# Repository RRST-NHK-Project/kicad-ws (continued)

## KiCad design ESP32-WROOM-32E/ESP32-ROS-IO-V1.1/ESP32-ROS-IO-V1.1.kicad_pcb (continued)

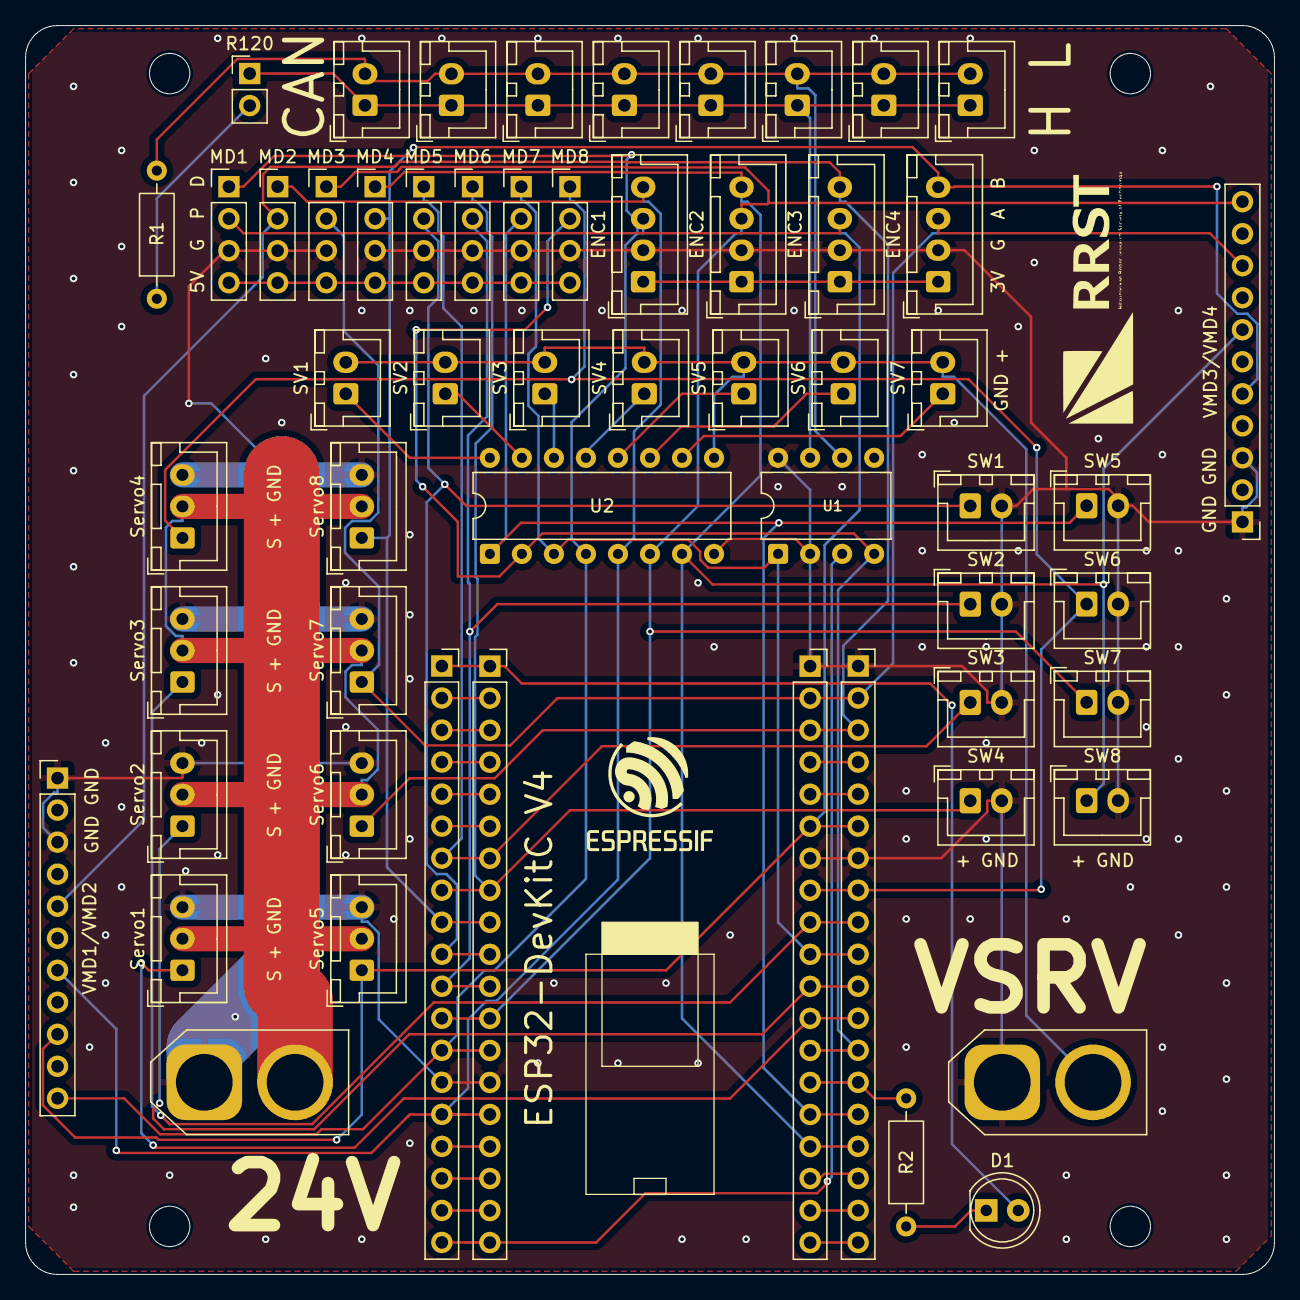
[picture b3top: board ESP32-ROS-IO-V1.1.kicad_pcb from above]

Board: 2 copper layers, 99.1 x 99.1 mm, 57 parts (0 on the bottom side), 51 nets.

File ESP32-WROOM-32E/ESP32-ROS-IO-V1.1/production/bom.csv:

Designator,Footprint,Quantity,Value,LCSC Part #
"CAN_BUS1, CAN_BUS2, CAN_BUS3, CAN_BUS4, CAN_BUS5, CAN_BUS6, CAN_BUS7, CAN_BUS8",JST_XH_B2B-XH-A_1x02_P2.50mm_Vertical,8,CAN_BUS,
D1,LED_D5.0mm,1,LED,
ENC1,JST_XH_B4B-XH-A_1x04_P2.50mm_Vertical,1,ENC1,
ENC2,JST_XH_B4B-XH-A_1x04_P2.50mm_Vertical,1,ENC2,
ENC3,JST_XH_B4B-XH-A_1x04_P2.50mm_Vertical,1,ENC3,
ENC4,JST_XH_B4B-XH-A_1x04_P2.50mm_Vertical,1,ENC4,
"J1, J2, J3, J4",PinSocket_1x19_P2.54mm_Vertical,4,Conn_01x19_Socket,
"J12, J13",AMASS_XT60-M_1x02_P7.20mm_Vertical,2,XT60-M,
MD1,PinHeader_1x04_P2.54mm_Vertical,1,MD1,
MD2,PinHeader_1x04_P2.54mm_Vertical,1,MD2,
MD3,PinHeader_1x04_P2.54mm_Vertical,1,MD3,
MD4,PinHeader_1x04_P2.54mm_Vertical,1,MD4,
MD5,PinHeader_1x04_P2.54mm_Vertical,1,MD5,
MD6,PinHeader_1x04_P2.54mm_Vertical,1,MD6,
MD7,PinHeader_1x04_P2.54mm_Vertical,1,MD7,
MD8,PinHeader_1x04_P2.54mm_Vertical,1,MD8,
R1,R_Axial_DIN0207_L6.3mm_D2.5mm_P10.16mm_Horizontal,1,120,
R120,PinHeader_1x02_P2.54mm_Vertical,1,R120,
R2,R_Axial_DIN0207_L6.3mm_D2.5mm_P10.16mm_Horizontal,1,330,
SERVO1,JST_XH_B3B-XH-A_1x03_P2.50mm_Vertical,1,Servo1,
SERVO2,JST_XH_B3B-XH-A_1x03_P2.50mm_Vertical,1,Servo2,
SERVO3,JST_XH_B3B-XH-A_1x03_P2.50mm_Vertical,1,Servo3,
SERVO4,JST_XH_B3B-XH-A_1x03_P2.50mm_Vertical,1,Servo4,
SERVO5,JST_XH_B3B-XH-A_1x03_P2.50mm_Vertical,1,Servo5,
SERVO6,JST_XH_B3B-XH-A_1x03_P2.50mm_Vertical,1,Servo6,
SERVO7,JST_XH_B3B-XH-A_1x03_P2.50mm_Vertical,1,Servo7,
SERVO8,JST_XH_B3B-XH-A_1x03_P2.50mm_Vertical,1,Servo8,
SV1,JST_XH_B2B-XH-A_1x02_P2.50mm_Vertical,1,SV1,
SV2,JST_XH_B2B-XH-A_1x02_P2.50mm_Vertical,1,SV2,
SV3,JST_XH_B2B-XH-A_1x02_P2.50mm_Vertical,1,SV3,
SV4,JST_XH_B2B-XH-A_1x02_P2.50mm_Vertical,1,SV4,
SV5,JST_XH_B2B-XH-A_1x02_P2.50mm_Vertical,1,SV5,
SV6,JST_XH_B2B-XH-A_1x02_P2.50mm_Vertical,1,SV6,
SV7,JST_XH_B2B-XH-A_1x02_P2.50mm_Vertical,1,SV7,
SW1,JST_XH_B2B-XH-A_1x02_P2.50mm_Vertical,1,SW1,
SW2,JST_XH_B2B-XH-A_1x02_P2.50mm_Vertical,1,SW2,
SW3,JST_XH_B2B-XH-A_1x02_P2.50mm_Vertical,1,SW3,
SW4,JST_XH_B2B-XH-A_1x02_P2.50mm_Vertical,1,SW4,
SW5,JST_XH_B2B-XH-A_1x02_P2.50mm_Vertical,1,SW5,
SW6,JST_XH_B2B-XH-A_1x02_P2.50mm_Vertical,1,SW6,
"SW7, SW8",JST_XH_B2B-XH-A_1x02_P2.50mm_Vertical,2,SW7,
U1,DIP-8_W7.62mm,1,~,
U2,DIP-16_W7.62mm,1,~,
VMD1/VMD2,PinHeader_1x11_P2.54mm_Vertical,1,VMD1/VMD2,
VMD3/VMD4,PinHeader_1x11_P2.54mm_Vertical,1,VMD3/VMD4,

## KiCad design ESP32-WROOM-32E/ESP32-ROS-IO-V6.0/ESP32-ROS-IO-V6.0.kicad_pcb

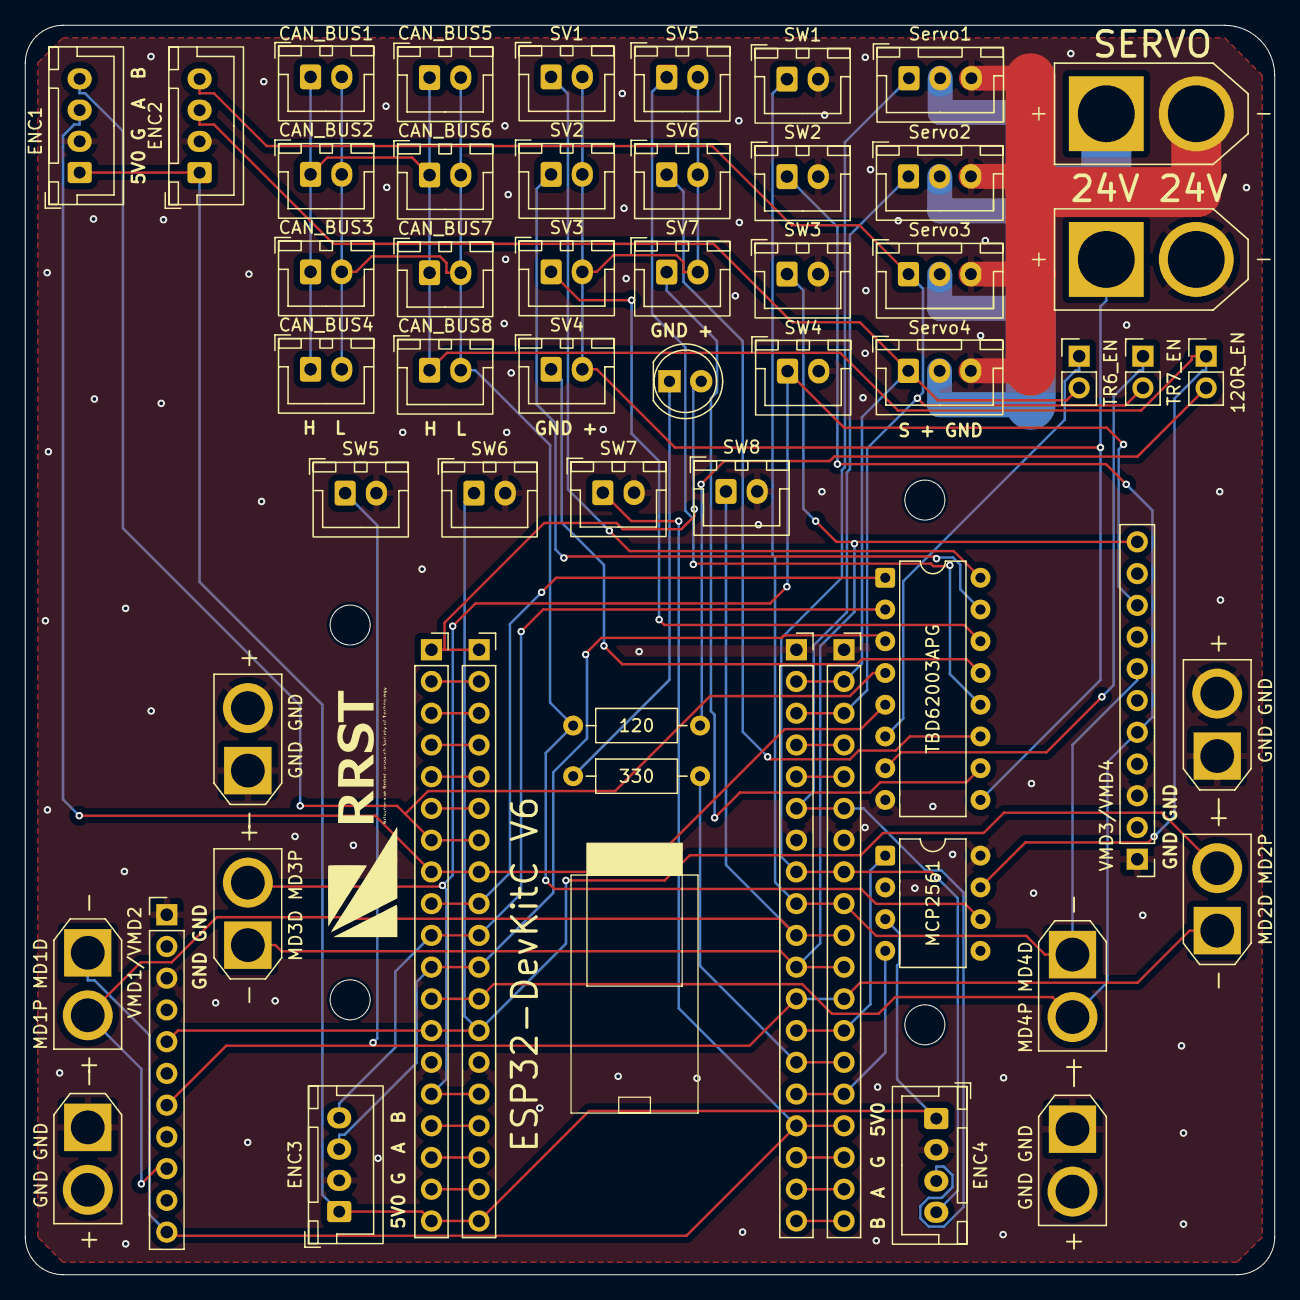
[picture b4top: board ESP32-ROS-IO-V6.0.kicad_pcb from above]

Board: 2 copper layers, 100.0 x 100.0 mm, 55 parts (0 on the bottom side), 51 nets.

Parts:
120R_EN: R120; PinHeader_1x02_P2.54mm_Vertical
CAN_BUS1, CAN_BUS2, CAN_BUS3, CAN_BUS4, CAN_BUS5, CAN_BUS6, CAN_BUS7, CAN_BUS8: CAN_BUS; JST_XH_B2B-XH-A_1x02_P2.50mm_Vertical
D1: LED; LED_D5.0mm
ENC1: ENC1; JST_XH_B4B-XH-A_1x04_P2.50mm_Vertical
ENC2: ENC2; JST_XH_B4B-XH-A_1x04_P2.50mm_Vertical
ENC3: ENC3; JST_XH_B4B-XH-A_1x04_P2.50mm_Vertical
ENC4: ENC4; JST_XH_B4B-XH-A_1x04_P2.50mm_Vertical
J1, J2, J3, J4: Conn_01x19_Socket; PinSocket_1x19_P2.54mm_Vertical
J16, J17: XT60-M; AMASS_XT60-M
MCP2561: DIP-8_W7.62mm
R1: 120; R_Axial_DIN0207_L6.3mm_D2.5mm_P10.16mm_Horizontal
R2: 330; R_Axial_DIN0207_L6.3mm_D2.5mm_P10.16mm_Horizontal
SV1: SV1; JST_XH_B2B-XH-A_1x02_P2.50mm_Vertical
SV2: SV2; JST_XH_B2B-XH-A_1x02_P2.50mm_Vertical
SV3: SV3; JST_XH_B2B-XH-A_1x02_P2.50mm_Vertical
SV4: SV4; JST_XH_B2B-XH-A_1x02_P2.50mm_Vertical
SV5: SV5; JST_XH_B2B-XH-A_1x02_P2.50mm_Vertical
SV6: SV6; JST_XH_B2B-XH-A_1x02_P2.50mm_Vertical
SV7: SV7; JST_XH_B2B-XH-A_1x02_P2.50mm_Vertical
SW1: SW1; JST_XH_B2B-XH-A_1x02_P2.50mm_Vertical
SW2: SW2; JST_XH_B2B-XH-A_1x02_P2.50mm_Vertical
SW3: SW3; JST_XH_B2B-XH-A_1x02_P2.50mm_Vertical
SW4: SW4; JST_XH_B2B-XH-A_1x02_P2.50mm_Vertical
SW5: SW5; JST_XH_B2B-XH-A_1x02_P2.50mm_Vertical
SW6: SW6; JST_XH_B2B-XH-A_1x02_P2.50mm_Vertical
SW7, SW8: SW7; JST_XH_B2B-XH-A_1x02_P2.50mm_Vertical
Servo1: Servo1; JST_XH_B3B-XH-A_1x03_P2.50mm_Vertical
Servo2: Servo2; JST_XH_B3B-XH-A_1x03_P2.50mm_Vertical
Servo3: Servo3; JST_XH_B3B-XH-A_1x03_P2.50mm_Vertical
Servo4: Servo4; JST_XH_B3B-XH-A_1x03_P2.50mm_Vertical
TBD62003APG: DIP-16_W7.62mm
TR6_EN, TR7_EN: Conn_01x02_Pin; PinHeader_1x02_P2.54mm_Vertical
VMD1: VMD1; AMASS_XT30U-F_1x02_P5.0mm_Vertical
VMD1/VMD2: VMD1/VMD2; PinHeader_1x11_P2.54mm_Vertical
VMD2: VMD2; AMASS_XT30U-F_1x02_P5.0mm_Vertical
VMD3: VMD3; AMASS_XT30U-F_1x02_P5.0mm_Vertical
VMD3/VMD4: VMD3/VMD4; PinHeader_1x11_P2.54mm_Vertical
VMD4: VMD4; AMASS_XT30U-F_1x02_P5.0mm_Vertical
VMDG1: VMDG1; AMASS_XT30U-F_1x02_P5.0mm_Vertical
VMDG2: VMDG2; AMASS_XT30U-F_1x02_P5.0mm_Vertical
VMDG3: VMDG3; AMASS_XT30U-F_1x02_P5.0mm_Vertical
VMDG4: VMDG4; AMASS_XT30U-F_1x02_P5.0mm_Vertical

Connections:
3V3: D1.2 (A), J1.1, J2.1
5V0: ENC1.1, ENC2.1, ENC3.1, ENC4.1, J1.19, J2.19, MCP2561.3 (Vdd)
+24V: J17.P (POS), SV1.2, SV2.2, SV3.2, SV4.2, SV5.2, SV6.2, SV7.2, TBD62003APG.9 (COMMON)
CANH: 120R_EN.1, CAN_BUS1.1, CAN_BUS2.1, CAN_BUS3.1, CAN_BUS4.1, CAN_BUS5.1, CAN_BUS6.1, CAN_BUS7.1, CAN_BUS8.1, MCP2561.7 (CANH)
CANL: CAN_BUS1.2, CAN_BUS2.2, CAN_BUS3.2, CAN_BUS4.2, CAN_BUS5.2, CAN_BUS6.2, CAN_BUS7.2, CAN_BUS8.2, MCP2561.6 (CANL), R1.1
CAN_RX: J3.15, J4.15, MCP2561.4 (Rxd)
CAN_TX: J3.13, J4.13, MCP2561.1 (Txd)
GND: ENC1.2, ENC2.2, ENC3.2, ENC4.2, J1.14, J2.14, J3.1, J3.7, J4.1, J4.7, J16.N (NEG), J17.N (NEG), MCP2561.2 (Vss), MCP2561.8 (STBY), SW1.2, SW2.2, SW3.2, SW4.2, SW5.2, SW6.2, SW7.2, SW8.2, Servo1.3, Servo2.3, Servo3.3, Servo4.3, TBD62003APG.8 (GND), VMD1/VMD2.1, VMD1/VMD2.3, VMD3/VMD4.1, VMD3/VMD4.3, VMDG1.1, VMDG1.2, VMDG2.1, VMDG2.2, VMDG3.1, VMDG3.2, VMDG4.1, VMDG4.2
GPIO0: J3.14, J4.14, R2.2
GPIO5: J3.10, J4.10, SW8.1, VMD1.2, VMD1/VMD2.9
GPIO12: J1.13, J2.13, SW6.1, VMD1/VMD2.5, VMD2.2
GPIO13: J1.15, J2.15, SW4.1, VMD3.2, VMD3/VMD4.9
GPIO14: J1.12, J2.12, SW2.1, VMD3/VMD4.5, VMD4.2
GPIO15: J3.16, J4.16, SW7.1, VMD1.1, VMD1/VMD2.11
GPIO16: J3.12, J4.12, SW5.1, VMD1/VMD2.7, VMD2.1
GPIO17: J3.11, J4.11, SW3.1, VMD3.1, VMD3/VMD4.11
GPIO18: J3.9, J4.9, SW1.1, VMD3/VMD4.7, VMD4.1
GPIO19: ENC4.4, J3.8, J4.8, Servo1.1
GPIO21: ENC4.3, J3.6, J4.6, Servo2.1
GPIO22: ENC2.4, J3.3, J4.3, Servo3.1, TR7_EN.2
GPIO23: ENC2.3, J3.2, J4.2, Servo4.1, TR6_EN.2
GPIO25: J1.9, J2.9, TBD62003APG.1 (I1)
GPIO26: ENC3.4, J1.10, J2.10, TBD62003APG.2 (I2)
GPIO27: ENC3.3, J1.11, J2.11, TBD62003APG.3 (I3)
GPIO32: ENC1.4, J1.7, J2.7, TBD62003APG.4 (I4)
GPIO33: ENC1.3, J1.8, J2.8, TBD62003APG.5 (I5)
NC1: J1.2, J2.2
NC2: J1.3, J2.3
NC3: J1.4, J2.4
NC4: J1.5, J2.5
NC5: J1.6, J2.6
NC6: J1.16, J2.16
NC7: J1.17, J2.17
NC8: J1.18, J2.18
NC9: J3.4, J4.4
NC10: J3.5, J4.5
NC11: J3.17, J4.17
NC12: J3.18, J4.18
NC13: J3.19, J4.19
unnamed: D1.1 (K), R2.1
unnamed: 120R_EN.2, R1.2
O1: SV1.1, TBD62003APG.16 (O1)
O2: SV2.1, TBD62003APG.15 (O2)
O3: SV3.1, TBD62003APG.14 (O3)
O4: SV4.1, TBD62003APG.13 (O4)
O5: SV5.1, TBD62003APG.12 (O5)
O6: SV6.1, TBD62003APG.11 (O6)
O7: SV7.1, TBD62003APG.10 (O7)
SERVO+: J16.P (POS), Servo1.2, Servo2.2, Servo3.2, Servo4.2
TR6: TBD62003APG.6 (I6), TR6_EN.1
TR7: TBD62003APG.7 (I7), TR7_EN.1
